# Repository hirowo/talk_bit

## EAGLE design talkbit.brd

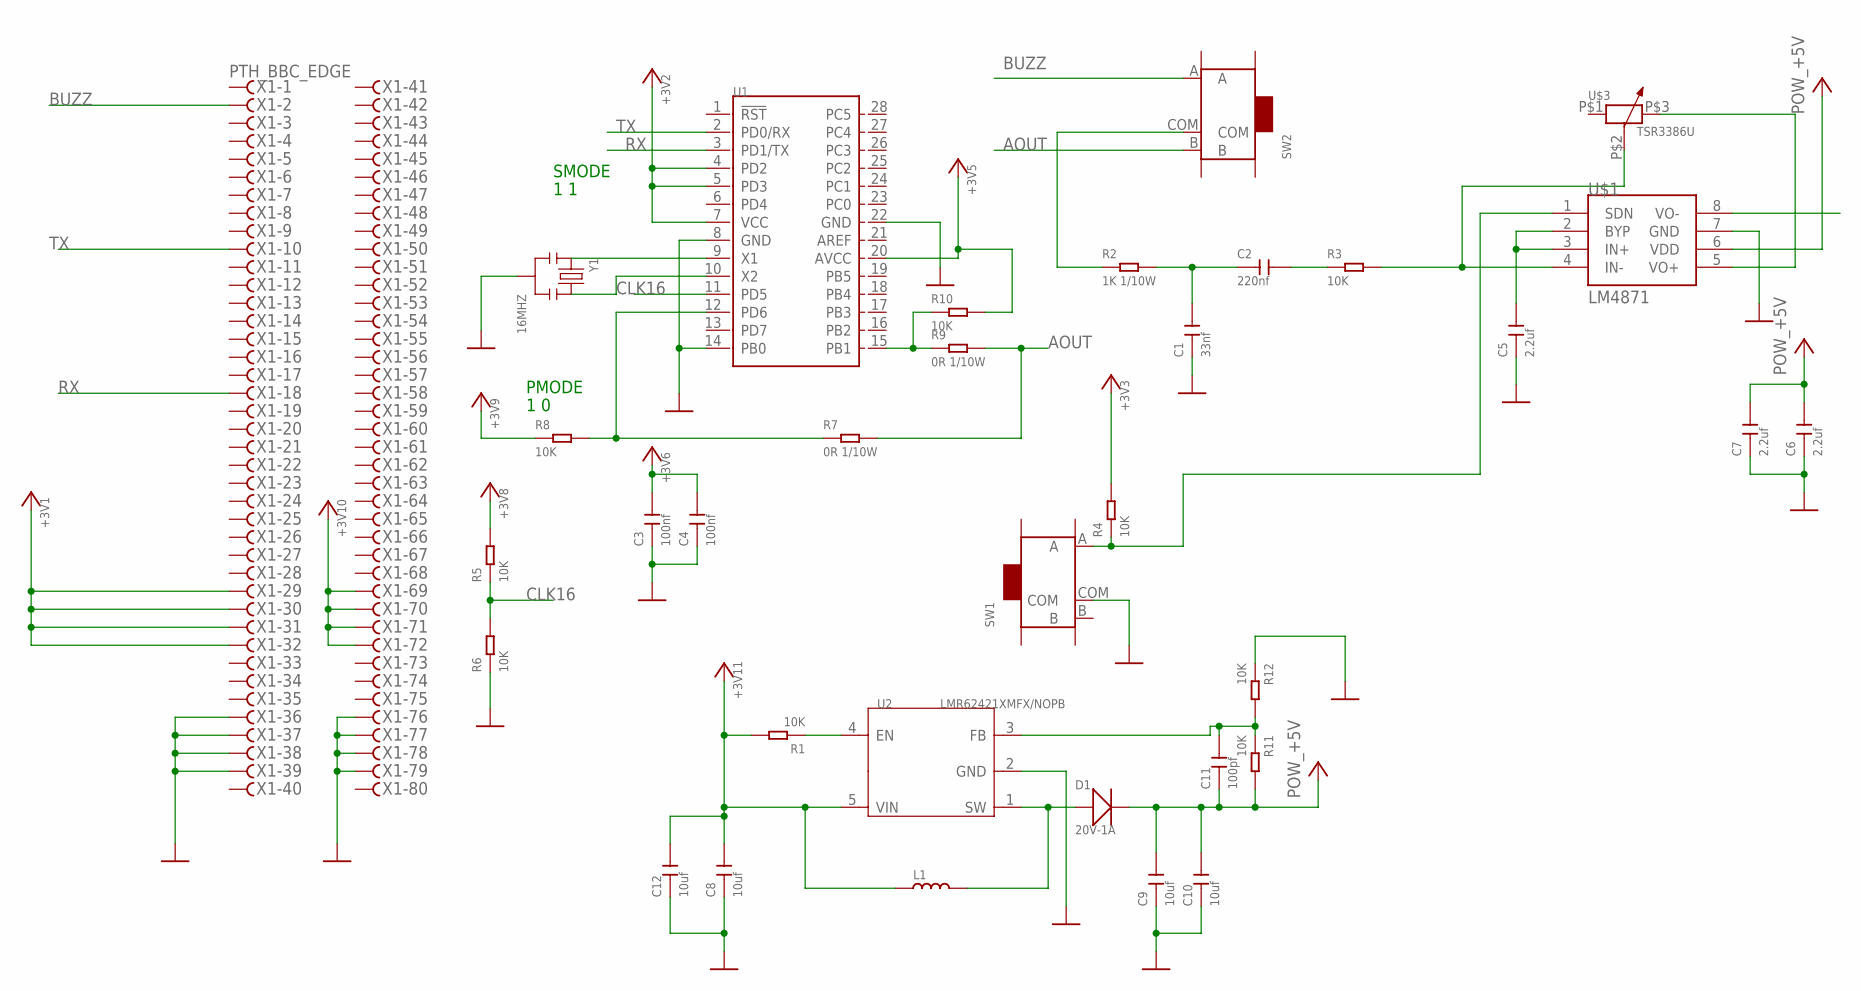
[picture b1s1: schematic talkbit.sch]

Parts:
C1: 33nf; C0603
C2: 220nf; C0603
C3, C4: 100nf; C0603
C5, C6, C7: 2.2uf; C0603
C8, C9, C10, C12: 10uf; C0603
C11: 100pf; C0603
D1: 20V-1A; SOD-123
L1: SMD-INDUCTOR-10UH-20%-2.35A(2P-5X5X4MM); L5040S
R1, R3, R4, R5, R6, R8, R10, R11, R12: 10K; R0603
R2: 1K 1/10W; R0603
R7, R9: 0R 1/10W; R0603
SW1, SW2: SMD-TOGGLE-SWITCH-ON-ON(3+4P-6.7X2.7MM); SW7-SMD-L6.7X2.7X3.2MM
U1: MCU-ATMEGA328P-PU(DIP28); DIP28-2.54-35.6X13.5MM
U2: LMR62421XMFX/NOPB; SOT-23-5
U$1: LM4871; SOIC8
U$3: TSR3386U; DIP3
X1: PTH_BBC_EDGE
Y1: 16MHZ; X3-SMD-3.6X1.3X0.8MM

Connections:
+3V3: C3.2, C4.2, C8.2, C12.2, L1.1, R1.2, R4.2, R5.2, R8.1, R10.2, U1.4 (PD2), U1.5 (PD3), U1.7 (VCC), U1.20 (AVCC), U2.5 (VIN), X1.29, X1.30, X1.31, X1.32, X1.69, X1.70, X1.71, X1.72
+5V: C6.2, C7.2, C9.2, C10.2, C11.1, D1.-, R11.2, U$1.6 (VDD)
AOUT: R7.2, R9.2, SW2.B
BUZZ: SW2.A, X1.2
CLK16: R5.1, R6.2, U1.11 (PD5)
GND: C1.1, C3.1, C4.1, C5.1, C6.1, C7.1, C8.1, C9.1, C10.1, C12.1, R6.1, R12.1, SW1.COM, U1.8 (GND), U1.14 (PB0), U1.22 (GND), U2.2 (GND), U$1.7 (GND), X1.36, X1.37, X1.38, X1.39, X1.76, X1.77, X1.78, X1.79, Y1.2
unnamed: C1.2, C2.1, R2.2
unnamed: C2.2, R3.1
unnamed: R3.2, U$1.4 (IN-), U$3.P$2 (3)
unnamed: R7.1, R8.2, U1.12 (PD6)
unnamed: C5.2, U$1.2 (BYP), U$1.3 (IN+)
unnamed: U$1.5 (VO+), U$3.P$3 (2)
unnamed: R4.1, SW1.A, U$1.1 (SDN)
unnamed: R2.1, SW2.COM
unnamed: U1.9 (X1), Y1.1
unnamed: U1.10 (X2), Y1.3
unnamed: R9.1, R10.1, U1.15 (PB1)
unnamed: R1.1, U2.4 (EN)
unnamed: C11.2, R11.1, R12.2, U2.3 (FB)
unnamed: D1.+, L1.2, U2.1 (SW)
RX: U1.3 (PD1/TX), X1.18
TX: U1.2 (PD0/RX), X1.10

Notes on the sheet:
SMODE
PMODE
1 1
1 0

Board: 2 copper layers, 34 parts (0 on the bottom side), 22 nets, no tracks yet.

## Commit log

2018-10-04 add new file
2018-10-04 gerver update 1st
